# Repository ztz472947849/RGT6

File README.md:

# Embedded Glue

A minimal system runs MicroPython using STM32F405RGT6

Designed in KiCAD, free to use in any application.

# Pics

PCB preview in KiCAD
</br>

</br>
Actual PCB
</br>

</br>
And the size of its stencil
</br>

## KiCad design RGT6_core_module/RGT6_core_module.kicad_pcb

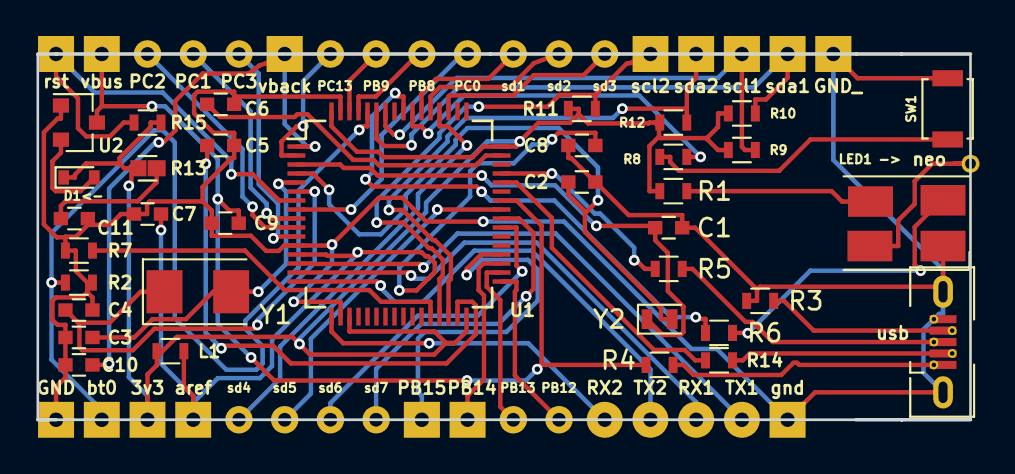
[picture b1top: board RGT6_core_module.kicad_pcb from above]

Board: 2 copper layers, 51.8 x 20.3 mm, 71 parts (0 on the bottom side), 54 nets.

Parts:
3v3: CONN_01X01_FEMALE; SolderWirePad_single_0-8mmDrill
C1, C2: 2p2; C_0603
C3, C4: 18p; C_0603
C5, C6: 2u2; C_0603
C7: 4u7; C_0603
C8: 100n; C_0603
C9: 1uF; C_0603
C10, C11: 100nF; C_0603
D1<-: DIODE; D_0603
GND: GND; SolderWirePad_single_0-8mmDrill
GND_: GND; SolderWirePad_single_0-8mmDrill
L1: 1k; L_0603
LED1 ->: WS2812B; ws2812_big-pad
PB8, PB9, PB12: CONN_01X01_FEMALE; testpoint
PB13, PB14, PB15: jtag; testpoint
PC0, PC1, PC2, PC3: ADCs; testpoint
PC13: do not use; testpoint
R1, R14: 300; R_0603
R2, R7: 100k; R_0603
R3, R4: 560; R_0603
R5, R6: 22; R_0603
R8, R9, R10, R11, R12, R15: 4k7; R_0603
R13: 220; R_0603_short
RX1: uart4 RX; SolderWirePad_single_0-8mmDrill
RX2: usart RX; SolderWirePad_single_0-8mmDrill
SW1: SW_Push; SW_SPST_B3U-1000P
TX1: uart4 TX; SolderWirePad_single_0-8mmDrill
TX2: usart TX; SolderWirePad_single_0-8mmDrill
U1: STM32F405RGTx; LQFP-64_10x10mm_Pitch0.5mm
U2: MCP1703A-4002_SOT23; SOT-23
Y1: 8Mhz; Crystal_SMD_5032-2pin_5.0x3.2mm
Y2: 32.768khz; Crystal_SMD_2012-2pin_2.0x1.2mm
aref: a3v3; testpoint
bt0: CONN_01X01_FEMALE; SolderWirePad_single_0-8mmDrill
gnd: GND; SolderWirePad_single_0-8mmDrill
neo: neo_out; SolderWirePad_single_0-8mmDrill
rst: CONN_01X01_FEMALE; SolderWirePad_single_0-8mmDrill
scl1, scl2: CONN_01X01_FEMALE; SolderWirePad_single_0-8mmDrill
sd1, sd2, sd3, sd4, sd5, sd6, sd7: CONN_01X01_FEMALE; testpoint
sda1, sda2: CONN_01X01_FEMALE; SolderWirePad_single_0-8mmDrill
usb: USB_OTG; my_usb
vback: CONN_01X01_FEMALE; SolderWirePad_single_0-8mmDrill
vbus: CONN_01X01_FEMALE; SolderWirePad_single_0-8mmDrill

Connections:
3.3v: 3v3.1, D1<-.1, L1.2, R1.1, R9.1, R10.1, R11.1, R12.1, R13.1, R15.2, U1.19, U1.32, U1.48, U1.64
A3v3: C7.2, C8.2, L1.1, U1.13, aref.1
D+: R5.1, U1.45
D-: R6.1, U1.44
unnamed: C1.1, U1.3, Y2.1
unnamed: C2.1, U1.4, Y2.2
unnamed: C3.2, U1.5, Y1.2
unnamed: C4.1, U1.6, Y1.1
unnamed: C5.1, U1.31
unnamed: C6.1, U1.47
unnamed: D1<-.2, U2.2
unnamed: R4.2, usb.1
unnamed: R6.2, usb.2
unnamed: R5.2, usb.3
unnamed: R3.1, usb.4
unnamed: LED1 ->.1, R1.2
unnamed: LED1 ->.4, R14.1
unnamed: R8.1, SW1.1
unnamed: R8.2, U1.55
PA0: TX1.1, U1.14
PA1: RX1.1, U1.15
PA2: TX2.1, U1.16
PA3: RX2.1, U1.17
PA8_sd: U1.41, sd5.1
PB4: R14.2, U1.56
PB8: PB8.1, U1.61
PB9: PB9.1, U1.62
PB12: PB12.1, U1.33
PB13: PB13.1, U1.34
PB14: PB14.1, U1.35
PB15: PB15.1, U1.36
PC0: PC0.1, U1.8
PC1: PC1.1, U1.9
PC2: PC2.1, U1.10
PC3: PC3.1, U1.11
PC8_sd: U1.39, sd6.1
PC9_sd: U1.40, sd7.1
PC10_sd: U1.51, sd3.1
PC11_sd: U1.52, sd4.1
PC12_sd: U1.53, sd2.1
PC13: PC13.1, U1.2
PD2_sd: U1.54, sd1.1
SCL1: R9.2, U1.58, scl1.1
SCL2: R11.2, U1.29, scl2.1
SDA1: R10.2, U1.59, sda1.1
SDA2: R12.2, U1.30, sda2.1
boot0: R2.1, U1.60, bt0.1
boot1: R7.2, U1.28
gnd: C1.2, C2.2, C3.1, C4.2, C5.2, C6.2, C7.1, C8.1, C9.1, C10.2, C11.2, GND.1, GND_.1, LED1 ->.3, R2.2, R3.2, R7.1, SW1.2, U1.12, U1.18, U1.63, U2.1, gnd.1, usb.5, usb.6
neo_out: LED1 ->.2, neo.1
rst: R15.1, U1.7, rst.1
v-battery: C11.1, R13.2
vbackup: C10.1, U1.1, vback.1
vbus: C9.2, R4.1, U1.42, U2.3, vbus.1

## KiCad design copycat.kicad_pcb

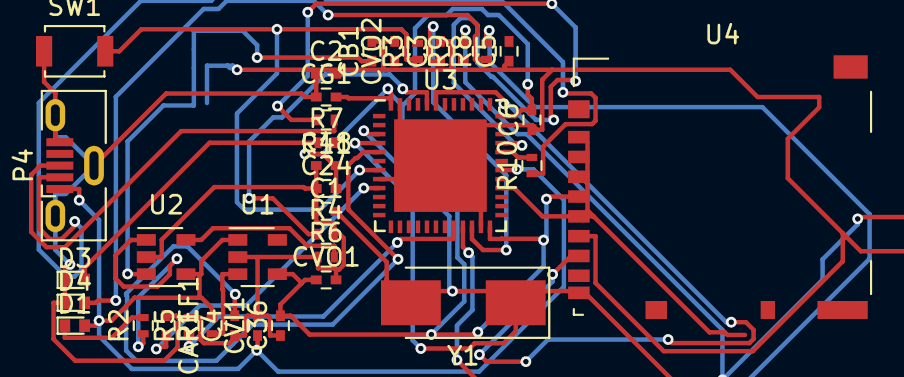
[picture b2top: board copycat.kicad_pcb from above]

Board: 2 copper layers, 37 parts (1 on the bottom side), 30 nets.

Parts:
C1, C2: 2.2pF; C_0402
C3: 2.2uF; C_0402
C4, C5: 18pF; C_0402
C6: 4.7uF; C_0402
C24, C36, C48: 0.1uF; C_0402
CAREF1: 0.1uF; C_0402
CB1: 10uF; C_0402
CG1: 4.7uF; C_0402
CVI1: 10uF; C_0402
CVO1: 10uF; C_0402
CVO2: 1uF; C_0402
D1: ORANGE; LED_0402
D3: RED; LED_0402
D4: BLUE; LED_0402
P2: CONN_01X02; JST_PH_S2B-PH-SM4-TB_02x2.00mm_Angled
P4: USB_OTG; USB_Micro-B_Vertical_Molex-105133-0001
R1, R4, R5: 100k; R_0402
R2: 1k; R_0402
R3: 4k7; R_0402
R6, R9: 10k; R_0402
R7: 560; R_0402
R8: 220; R_0402
R10, R11: 22; R_0402
SW1: RST; SW_SPST_B3U-1000P
U1: SPX3819; SOT-23-5
U2: MCP73811T-420I/OT; SOT-23-5
U3: STM32F411CEUx; QFN-48-1EP_7x7mm_Pitch0.5mm
U4: MicroSD_SPI_CD; microSD_Card_Receptacle_Hirose_DM3AT-SF-PEJM5
Y1: 32.768Hz; Crystal_SMD_0603-2pin_6.0x3.5mm_HandSoldering

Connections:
+3V3: C6.2, C24.2, C36.2, C48.2, CG1.2, CVO1.1, CVO2.1, R3.2, R9.1, U1.4, U3.24, U3.36, U3.48, U4.4
AREF: CAREF1.2, U3.9
BOOT0: R4.1, U3.44
CD: R9.2, U4.9
DI: U3.16, U4.3
DO: U3.43, U4.7
EN: R1.1, U1.3
GND: C1.1, C2.1, C3.2, C4.1, C5.1, C6.1, C24.1, C36.1, C48.1, CAREF1.1, CB1.2, CG1.1, CVI1.2, CVO1.2, CVO2.2, D3.1, D4.1, P2.1, P4.5, P4.6, R4.2, R5.2, R6.1, SW1.1, U1.2, U2.2, U3.8, U3.23, U3.35, U3.47, U3.49, U4.6
IO0: R8.2, U3.21
IO1: R7.2, U3.27
unnamed: C3.1, U3.22
unnamed: D1.1, R2.2
unnamed: D3.2, R7.1
unnamed: D4.2, R8.1
unnamed: P4.2, R10.1
unnamed: P4.3, R11.1
unnamed: P4.4, U3.31
unnamed: R2.1, U2.1
unnamed: R5.1, U3.20
unnamed: R6.2, U2.5
unnamed: R10.2, U3.32
unnamed: R11.2, U3.33
OSC32IN: C1.2, U3.3, Y1.2
OSC32OUT: C2.2, U3.4, Y1.1
OSCIN: C4.2, U3.5
OSCOUT: C5.2, U3.6
RST: R3.1, SW1.2, U3.7
SCLK: U3.28, U4.5
VBAT: CB1.1, P2.2, U2.3
VBUS: CVI1.1, D1.2, P4.1, R1.2, U1.1, U2.4, U3.30

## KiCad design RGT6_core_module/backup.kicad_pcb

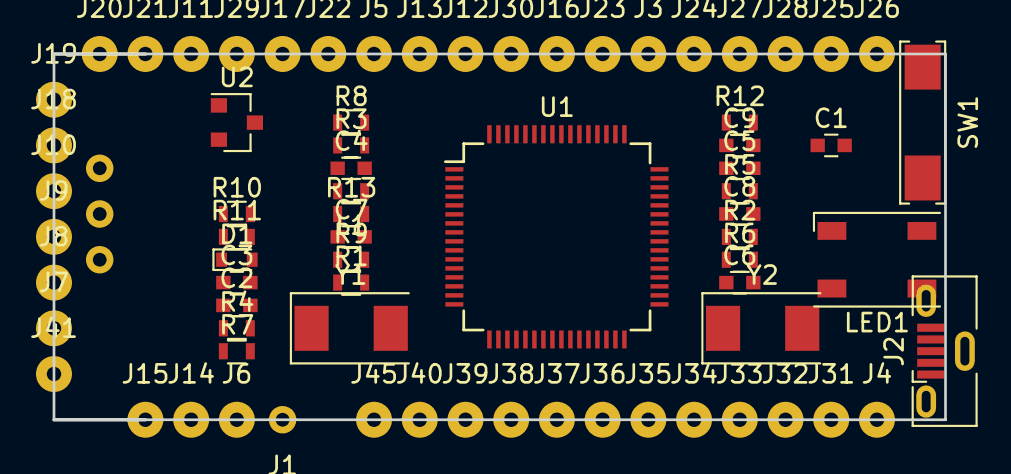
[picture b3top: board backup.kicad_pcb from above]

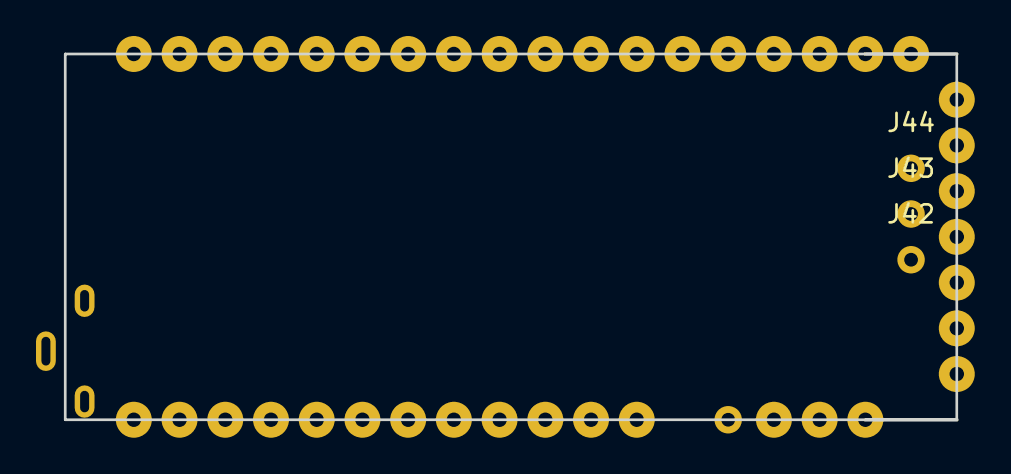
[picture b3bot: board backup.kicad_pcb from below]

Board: 2 copper layers, 49.5 x 20.3 mm, 75 parts (3 on the bottom side), 58 nets, no tracks yet.

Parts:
C1, C2: 2p2; C_0603
C3, C4: 18p; C_0603
C5, C6: 2u2; C_0603
C7: 4u7; C_0603
C8: 100n; C_0603
C9: C; C_0603
D1: DIODE; D_0603
J1: a3v3; testpoint
J2: USB_OTG; USB_Micro-B_Vertical_Molex-105133-0001
J3, J5, J6, J7, J8, J9, J10, J11, J12, J13, J14, J15, J18, J19, J23, J24, J25, J26, J27, J28, J41, J45: CONN_01X01_FEMALE; SolderWirePad_single_0-8mmDrill
J4: GND; SolderWirePad_single_0-8mmDrill
J16, J20, J21, J22: ADCs; SolderWirePad_single_0-8mmDrill
J17: do not use; SolderWirePad_single_0-8mmDrill
J29, J30, J39, J40: IOs; SolderWirePad_single_0-8mmDrill
J31, J35: usart TX; SolderWirePad_single_0-8mmDrill
J32, J36: usart RX; SolderWirePad_single_0-8mmDrill
J33: uart4 TX; SolderWirePad_single_0-8mmDrill
J34: uart4 RX; SolderWirePad_single_0-8mmDrill
J37, J38: DACs; SolderWirePad_single_0-8mmDrill
J42, J43, J44: jtag; testpoint
L1: 1k; L_0603
LED1: WS2812B; LED_WS2812B-PLCC4
R1: 300; R_0603
R2, R7: 100k; R_0603
R3, R4: 560; R_0603
R5, R6: 22; R_0603
R8, R9, R10, R11, R12: 4k7; R_0603
R13: 220; R_0603
SW1: SW_Push; SW_SPST_REED_CT05-XXXX-J1
U1: STM32F405RGTx; LQFP-64_10x10mm_Pitch0.5mm
U2: MCP1703A-4002_SOT23; SOT-23
Y1: 8Mhz; Crystal_SMD_0603-2pin_6.0x3.5mm
Y2: 32.768khz; Crystal_SMD_0603-2pin_6.0x3.5mm

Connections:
3.3v: D1.1, J6.1, L1.2, R1.1, R9.1, R10.1, R11.1, R12.1, R13.1, U1.7, U1.19, U1.32, U1.48, U1.64
A3v3: C7.2, C8.2, J1.1, L1.1, U1.13
D+: R5.1, U1.45
D-: R6.1, U1.44
unnamed: C1.1, U1.3, Y2.1
unnamed: C2.1, U1.4, Y2.2
unnamed: C3.2, U1.5, Y1.2
unnamed: C4.1, U1.6, Y1.1
unnamed: C5.1, U1.31
unnamed: C6.1, U1.47
unnamed: D1.2, U2.2
unnamed: J2.1, R4.2
unnamed: J2.2, R6.2
unnamed: J2.3, R5.2
unnamed: J2.4, R3.1
unnamed: LED1.1, R1.2
unnamed: R8.1, SW1.1
unnamed: R8.2, U1.55
PA0: J33.1, U1.14
PA1: J34.1, U1.15
PA2: J35.1, U1.16
PA3: J36.1, U1.17
PA4: J37.1, U1.20
PA5: J38.1, U1.21
PA6: J39.1, U1.22
PA7: J40.1, U1.23
PA8_sd: J41.1, U1.41
PB4: LED1.4, U1.56
PB8: J11.1, J23.1, U1.61
PB9: J12.1, J24.1, U1.62
PB12: J13.1, U1.33
PB13: J42.1, U1.34
PB14: J43.1, U1.35
PB15: J44.1, U1.36
PC0: J16.1, U1.8
PC1: J20.1, U1.9
PC2: J21.1, U1.10
PC3: J22.1, U1.11
PC4: J29.1, U1.24
PC5: J30.1, U1.25
PC6: J31.1, U1.37
PC7: J32.1, U1.38
PC8_sd: J8.1, U1.39
PC9_sd: J9.1, U1.40
PC10_sd: J10.1, U1.51
PC11_sd: J19.1, U1.52
PC12_sd: J18.1, U1.53
PC13: J17.1, U1.2
PD2_sd: J7.1, U1.54
SCL1: J25.1, R9.2, U1.58
SCL2: J27.1, R11.2, U1.29
SDA1: J26.1, R10.2, U1.59
SDA2: J28.1, R12.2, U1.30
boot0: J14.1, R2.1, U1.60
boot1: J15.1, R7.2, U1.28
gnd: C1.2, C2.2, C3.1, C4.2, C5.2, C6.2, C7.1, C8.1, C9.1, J2.5, J2.6, J4.1, LED1.3, R2.2, R3.2, R7.1, SW1.2, U1.12, U1.18, U1.63, U2.1
vbat: J5.1, R13.2, U1.1
vbus: C9.2, R4.1, U1.42, U2.3

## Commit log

2017-09-08 no message
